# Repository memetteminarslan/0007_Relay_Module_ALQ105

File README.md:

# 0007_Relay_Module_ALQ105
You are seeing a large number of widely used Relay modules in electronic development kits. More information coming soon...

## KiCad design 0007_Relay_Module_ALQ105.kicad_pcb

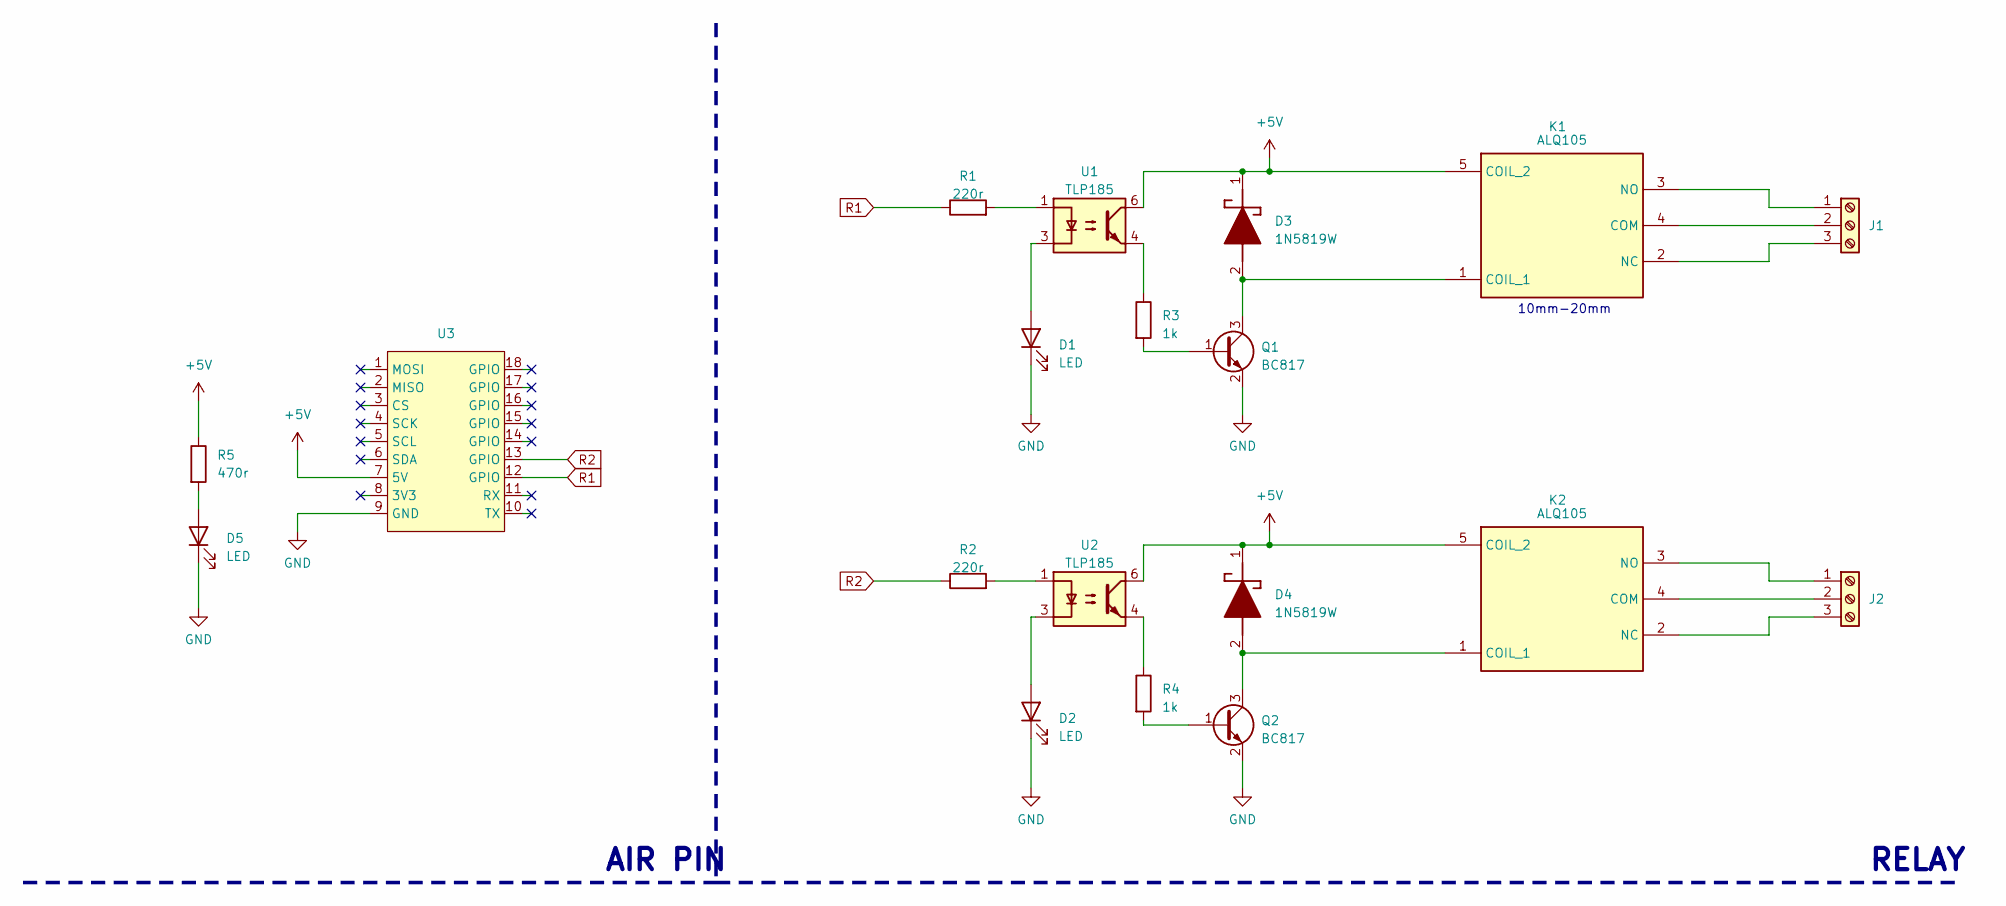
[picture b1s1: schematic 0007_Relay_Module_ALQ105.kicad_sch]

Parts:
D1, D2, D5: LED; LED_0805_2012Metric
D3, D4: 1N5819W; SODFL3618X110N; Manufacturer_Part_Number 1N5819W
J1, J2: Screw_Terminal_01x03; TerminalBlock_4Ucon_1x03_P3.50mm_Horizontal
K1, K2: ALQ105; Mouser Part Number 769-ALQ105
Q1, Q2: BC817; SOT-23
R1, R2: 220r; R_0805_2012Metric
R3, R4: 1k; R_0805_2012Metric
R5: 470r; R_0805_2012Metric
U1, U2: TLP185; SOIC-4_4.55x3.7mm_P2.54mm
U3: air__module

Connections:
+5V: D3.1 (K), D4.1 (K), K1.5 (COIL_2), K2.5 (COIL_2), R5.1, U1.6, U2.6, U3.7 (5V)
GND: D1.1 (K), D2.1 (K), D5.1 (K), Q1.2 (E), Q2.2 (E), U3.9 (GND)
unnamed: D1.2 (A), U1.3
unnamed: D2.2 (A), U2.3
unnamed: D3.2 (A), K1.1 (COIL_1), Q1.3 (C)
unnamed: D4.2 (A), K2.1 (COIL_1), Q2.3 (C)
unnamed: D5.2 (A), R5.2
unnamed: J1.1, K1.3 (NO)
unnamed: J1.2, K1.4 (COM)
unnamed: J1.3, K1.2 (NC)
unnamed: J2.1, K2.3 (NO)
unnamed: J2.2, K2.4 (COM)
unnamed: J2.3, K2.2 (NC)
unnamed: Q1.1 (B), R3.2
unnamed: Q2.1 (B), R4.2
unnamed: R1.2, U1.1
unnamed: R2.2, U2.1
unnamed: R3.1, U1.4
unnamed: R4.1, U2.4
R1: R1.1, U3.12 (GPIO)
R2: R2.1, U3.13 (GPIO)

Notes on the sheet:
10mm-20mm
RELAY
AIR PIN

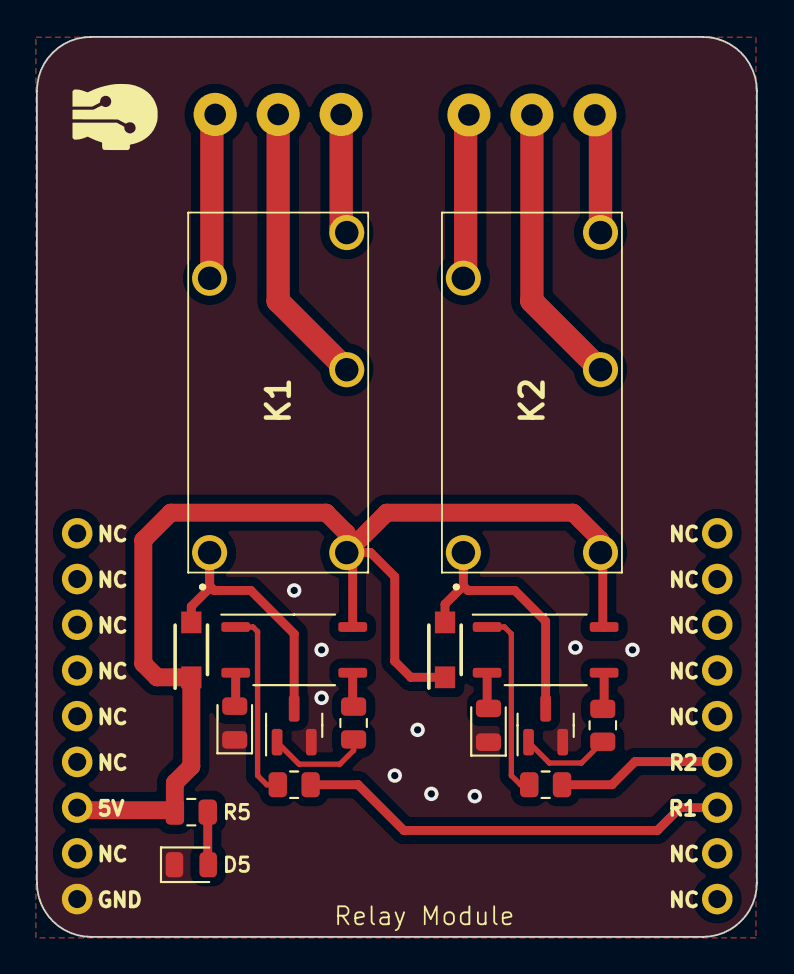
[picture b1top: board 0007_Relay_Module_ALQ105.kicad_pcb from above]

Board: 2 copper layers, 40.0 x 50.0 mm, 19 parts (0 on the bottom side), 21 nets.
